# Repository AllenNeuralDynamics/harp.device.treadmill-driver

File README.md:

A Harp Device for controlling an instrumented variable-friction mouse treadmill

> [!NOTE]
> This repository contains design files for the electronics assembly. For the mechanical assembly, design files, and bill-of-materials, see the [OnShape project](https://cad.onshape.com/documents/579ff6de692121d8b6a45604/v/23e1e086e9eb645d096dac80/e/a0ad881c32324c0acf8e15df).

> [!IMPORTANT]
> This version runs on a Raspberry Pi Pico that slots into a carrier board with an encoder input plug and a Harp Sync plug.
> The magnetic brake and torque sensor are **disabled**.
> Their registers are kept so that existing software for the treadmill-driver keeps working: torque and brake current read as 0, and brake and torque-limit settings are accepted but have no effect.

## Features
* runs on a Raspberry Pi Pico mounted on a carrier board.
* quadrature encoder input for position/speed measurements, with logic-level shifting.
* Harp-protocol compliant over full-speed USB.
* accepts Harp time synchronization input.
* register-compatible with the original treadmill-driver (WhoAmI 1402).

## Register Map
[List of Registers](./firmware/docs/register_map.csv)

## Credits
The original board design was created in partnership with the team at [Second Order Effects](https://soeffects.com/).

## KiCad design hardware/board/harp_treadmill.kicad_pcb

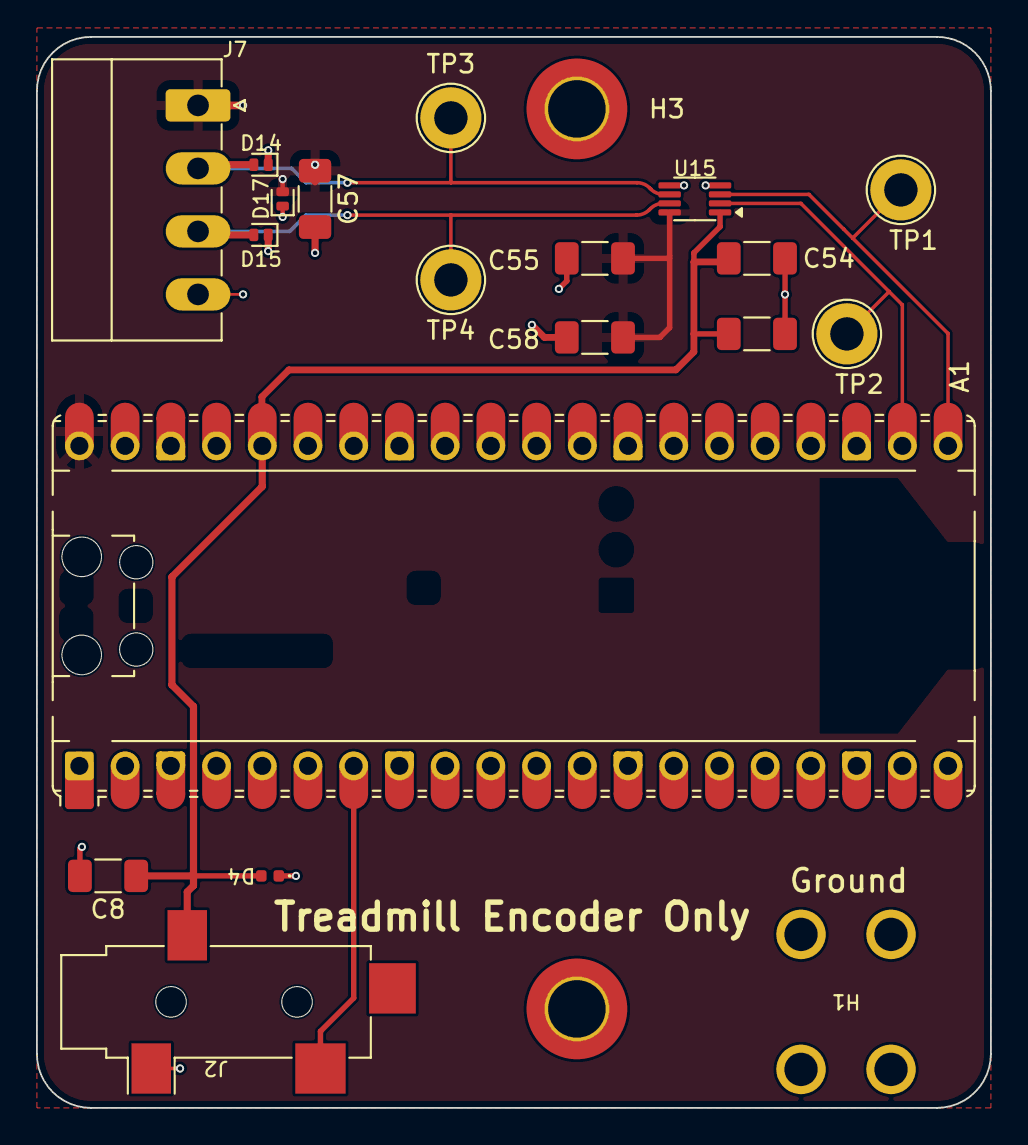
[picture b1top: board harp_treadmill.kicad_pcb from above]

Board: 2 copper layers, 53.0 x 59.5 mm, 21 parts (0 on the bottom side), 8 nets.

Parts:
A1: RaspberryPi_Pico; RaspberryPi_Pico_Common_Unspecified
C8, C54, C55: 1uF; C_1206_3216Metric_Pad1.33x1.80mm_HandSolder
C53, C58: 100nF; C_1206_3216Metric_Pad1.33x1.80mm_HandSolder
C57: 10uF; C_1206_3216Metric_Pad1.33x1.80mm_HandSolder
D4: D_TVS; D_0402_1005Metric
D14, D15, D17: D_TVS; D_SOD-882D
H1: MountingHole_Pad; Terminal_Keystone_779x_EdgeMount_Horizontal
H2, H3: MountingHole_Pad; MountingHole_3.2mm_M3_DIN965_Pad_TopBottom
J2: AudioJack3; Jack_3.5mm_CUI_SJ-3524-SMT_Horizontal
J7: Conn_01x04_Female; PhoenixContact_MC_1,5_4-G-3.5_1x04_P3.50mm_Horizontal
TP1, TP2, TP3, TP4: TestPoint; TestPoint_Loop_D2.50mm_Drill1.85mm
U15: 74LVCH2T45DC; VSSOP-8_2.3x2mm_P0.5mm

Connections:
+3V3: A1.36 (3V3), C8.1, C53.2, C54.1, D4.2 (A2), J2.R, U15.1 (VCCA)
+5V: A1.40 (VBUS), C55.1, C57.1, C58.2, D17.2 (A2), J7.1, U15.8 (VCCB)
/ENC_A: A1.21 (GPIO16), TP1.1, U15.3 (2A)
/ENC_B: A1.22 (GPIO17), TP2.1, U15.2 (1A)
/HARP_CLK_SYNC: A1.7 (GPIO5), J2.T
GND: A1.3 (GND), A1.8 (GND), A1.13 (GND), A1.18 (GND), A1.23 (GND), A1.28 (GND), A1.38 (GND), C8.2, C53.1, C54.2, C55.2, C57.2, C58.1, D4.1 (A1), D14.1 (A1), D15.1 (A1), D17.1 (A1), H1.1, H2.1, H3.1, J2.S, J7.4, U15.4 (GND), U15.5 (DIR)
unnamed: D14.2 (A2), J7.2, TP3.1, U15.6 (2B)
unnamed: D15.2 (A2), J7.3, TP4.1, U15.7 (1B)

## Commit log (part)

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2023-04-10 add schematic draft
2023-04-11 update cmakelists to compile harp core
2023-04-14 draft torque load sensing in schematic
2023-04-15 adc reading works
2023-05-09 debug port works; draft current driver
2023-05-09 add preliminary register map.
2023-10-17 rename git submodule
2023-10-18 update board schematic
2023-10-19 update pcb
2023-10-20 update schematic
2023-10-26 update sch and pcb
2023-10-27 update schematic; continue pcb draft
2023-10-27 wrap up pcb draft
2023-10-27 update hw license
2023-10-27 add notes
2023-10-30 update schematic annotation
2023-11-09 draft layout with analog brake driver circuit
2023-11-14 draft v0.1 pcb
2023-12-06 draft firmware
2023-12-11 draft main.cpp
2023-12-14 draft of firmware works
2023-12-22 fix 12-bit adc bug
2023-12-22 remove embedded submodule
2023-12-22 add adc lib submodule and remove pico sdk submodule
2024-01-10 add cad v0.2.0 step model
2024-01-10 draft lid
2024-01-10 add lids
2024-01-10 update lids
2024-01-10 add lid dxfs
2024-01-12 add firmware license
2024-02-27 Add first draft of interface
2024-03-06 Update according to new specs
2024-03-06 Improve clarity
2024-03-06 Fix package metadata
2024-03-06 Regenerate interface
2024-03-08 update register draft
2024-03-08 add bulk sensor reading example
2024-03-08 adding untare capability
2024-03-08 add separate read-sensor example
2024-03-08 update tare register
2024-03-08 fix event register update bug
2024-03-08 Update schema
2024-03-08 Add register metadata
2024-03-08 update comment
2024-03-21 Standardize folder structure across allen devices
2024-06-14 add comment about race condition
2024-06-14 bugfix uart port
2024-07-18 Fix data format for DispatchRate register
2024-07-18 Bump package
2024-07-18 draft torque limiting
2024-07-18 update torque limiting logic
2024-07-18 prevent EVENT msg spam when torque limit triggered.
2024-07-24 append git has to executable name
2024-07-25 add filter to torque limit sensing; bugfix reg_count
2024-07-26 offset treadmill limits
2024-07-26 add pyharp examples
2024-07-29 migrate ltc264x lib to submodule
2024-08-13 add code comment
2024-08-13 draft brake calibration scripts
2024-08-20 draft brake calibration code
2024-08-20 update silkscreen size; add mating connector note
2024-08-20 update brake calibration script
2024-08-21 draft working calibration script
2024-08-21 Update device spec to latest firmware updates
2024-08-21 Remove string literals
2024-08-21 Regenerate interfaces
2024-08-21 Update package metadata with release
2024-08-21 add requirements.txt
2024-08-21 update calibration readme
2024-08-21 Clarify default behavior of EnableTorqueLimit register
2024-08-21 get writing settings working
2024-08-24 add calibration output-to-csv option
2024-08-26 update calibration script
2024-08-26 add slow sleep
2024-08-26 add duration calculation info msg
2024-08-27 add trim to enclosure
2024-09-24 draft curve fit
2024-09-25 update pcb and schematic
2024-09-25 update harp core and add hw/fw version to harp core
2024-09-26 add frontfacing images
2024-10-02 update for windows compatibility
2024-10-11 add rrio note about ad8226
2024-11-08 Update bonsai generators
2024-11-09 Fix schema source
2024-11-10 Favor harp-tech as source of device schema
2025-02-11 update harp core & bump version
2025-02-11 add description to usb-descriptors
2025-02-11 update version number
